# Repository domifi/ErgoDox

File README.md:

# Information
This repo is a fork of the ErgoDox Mechanical Keyboard pcb and Litster's acrylic case designs (both standard and full hand).

This variation of the design has a two main goals:
* Replace the Mini B port with a Type C port while maintaining reversibility of the PCB design.
* Keep the rest of the design as unchanged as possible.
  - The idea is that most case designs should still be compatible (with at most minor adjustments)

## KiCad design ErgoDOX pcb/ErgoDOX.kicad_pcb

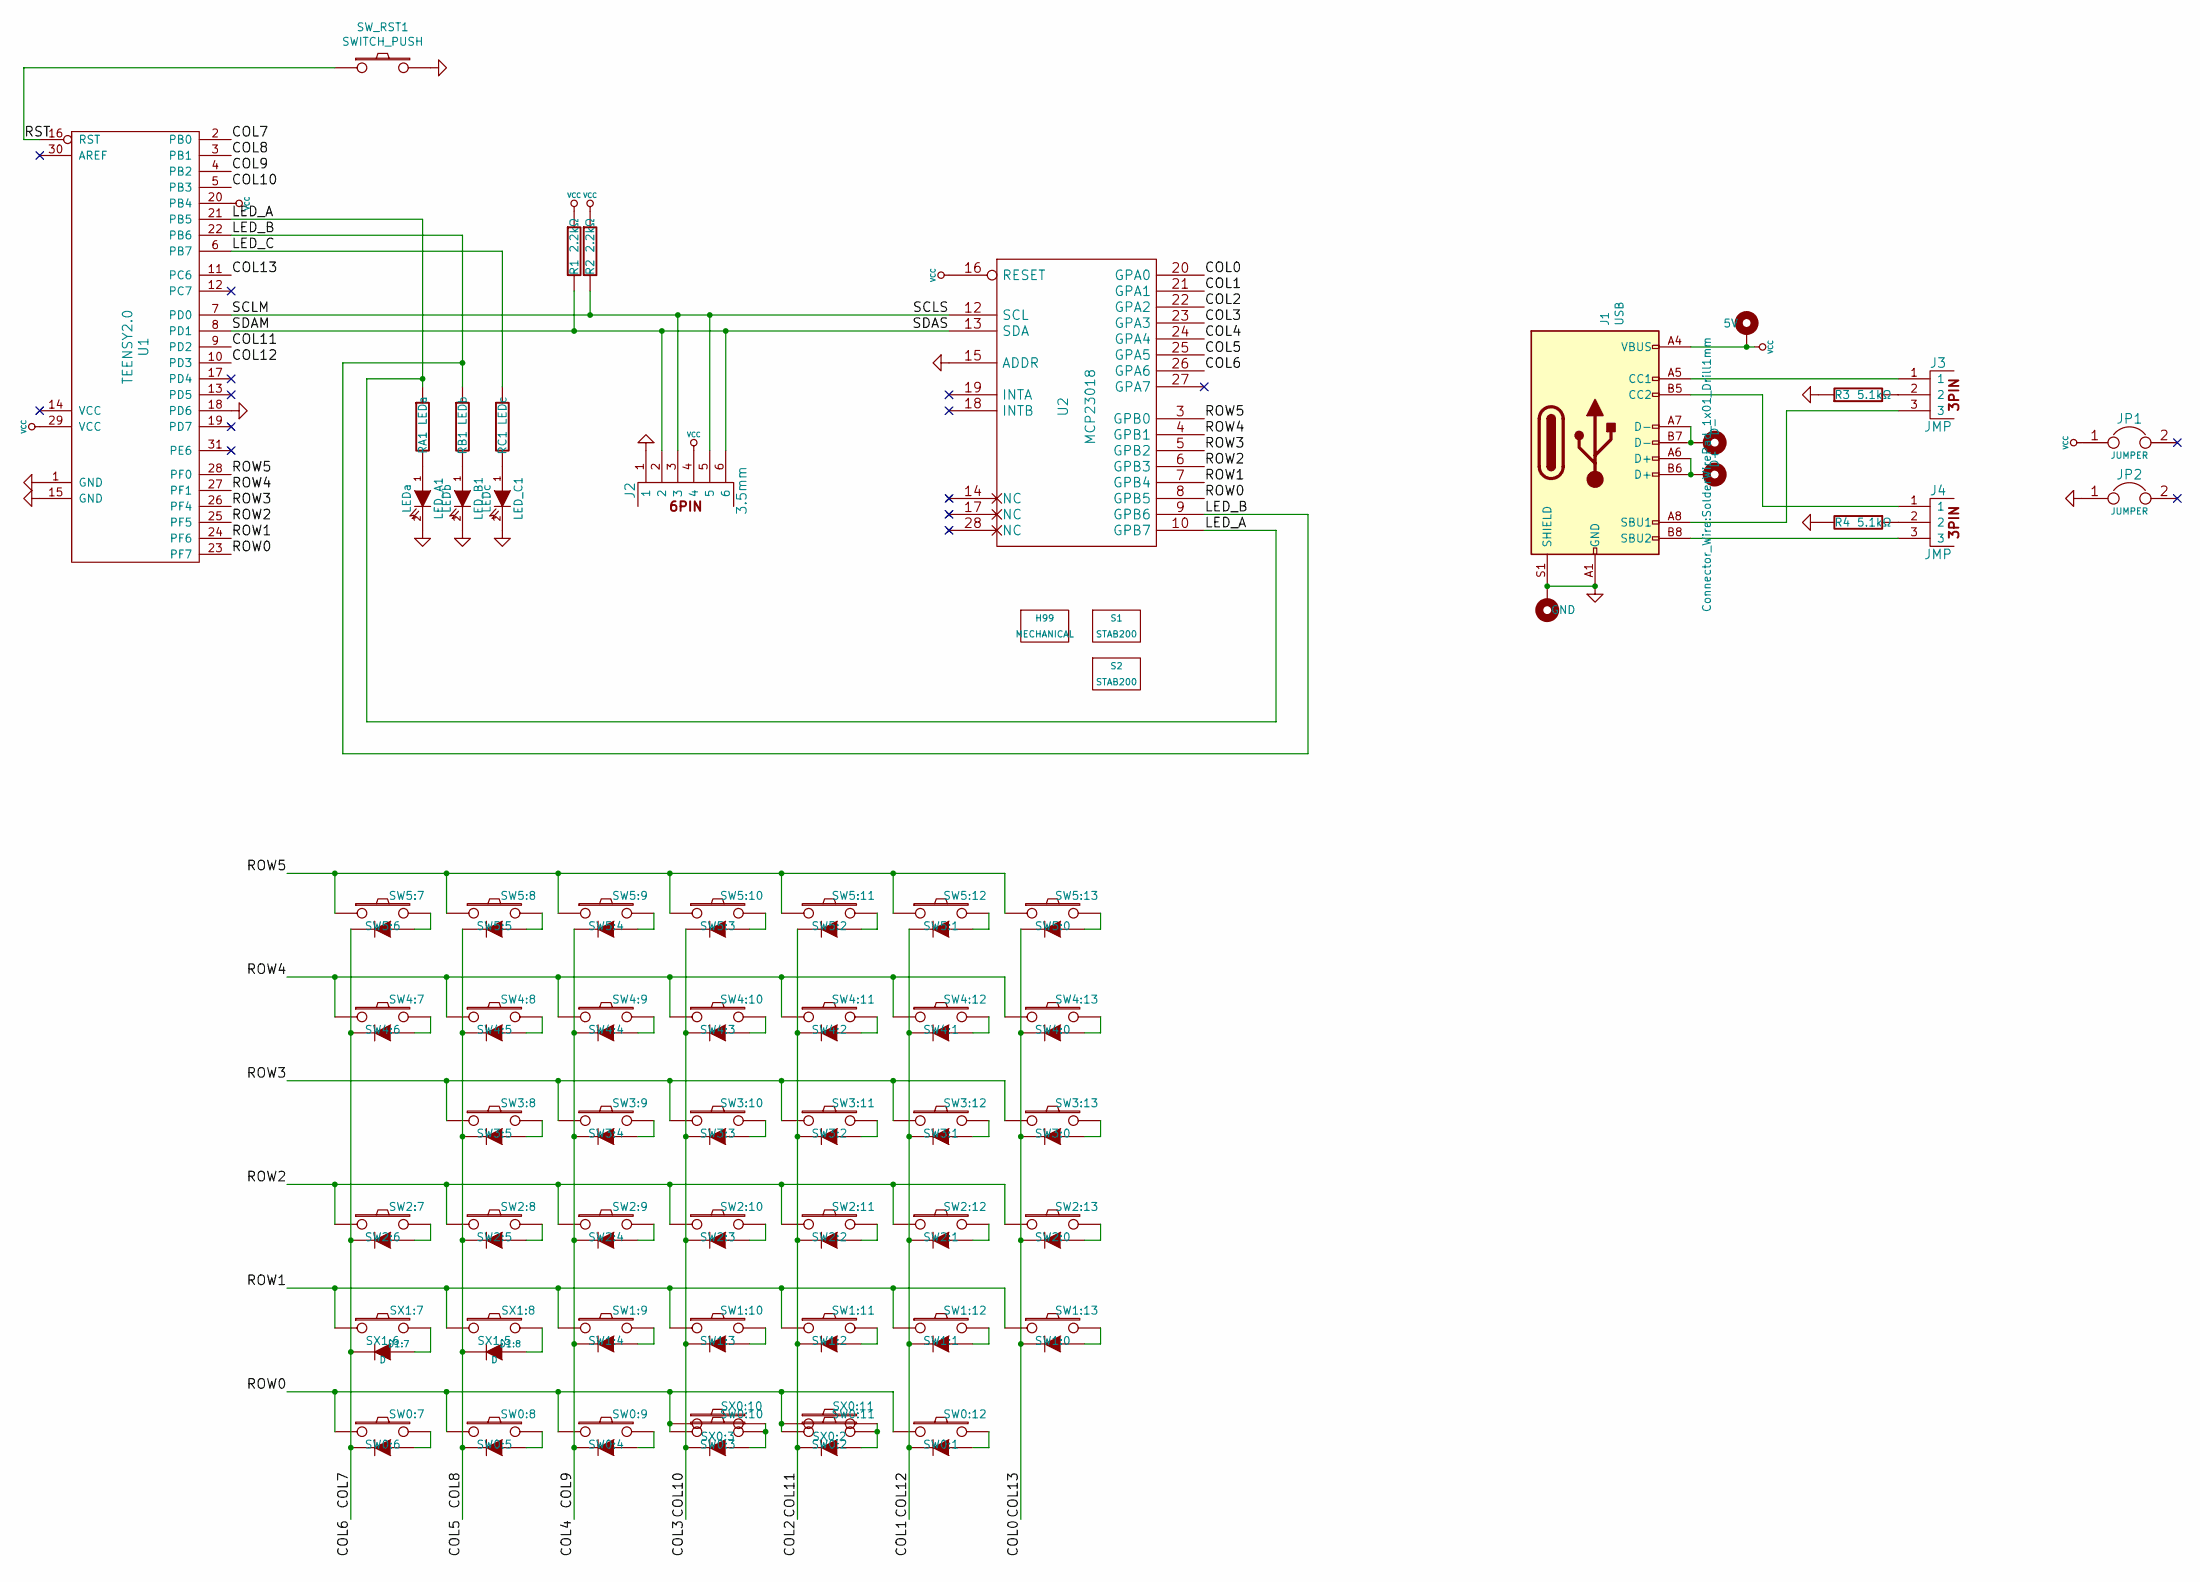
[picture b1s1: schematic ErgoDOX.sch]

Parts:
D1:7, D1:8: D
H1: D+; SolderWirePad_1x01_Drill1mm
H2: D-; SolderWirePad_1x01_Drill1mm
H3: 5V; SolderWirePad_1x01_Drill1mm
H4: GND; SolderWirePad_1x01_Drill1mm
H99: MECHANICAL
J1: USB; USB_C_Receptacle_GCT_USB4085
J2: 3.5mm
J3, J4: JMP
JP1, JP2: JUMPER
LED_A1: LEDa
LED_B1: LEDb
LED_C1: LEDc
R1, R2: 2.2kΩ
R3, R4: 5.1kΩ; R_Axial_DIN0207_L6.3mm_D2.5mm_P10.16mm_Horizontal
RA1: LEDa
RB1: LEDb
RC1: LEDc
S1, S2: STAB200
SW0:7: SW0:6
SW0:8: SW0:5
SW0:9: SW0:4
SW0:10: SW0:3
SW0:11: SW0:2
SW0:12: SW0:1
SW1:9: SW1:4
SW1:10: SW1:3
SW1:11: SW1:2
SW1:12: SW1:1
SW1:13: SW1:0
SW2:7: SW2:6
SW2:8: SW2:5
SW2:9: SW2:4
SW2:10: SW2:3
SW2:11: SW2:2
SW2:12: SW2:1
SW2:13: SW2:0
SW3:8: SW3:5
SW3:9: SW3:4
SW3:10: SW3:3
SW3:11: SW3:2
SW3:12: SW3:1
SW3:13: SW3:0
SW4:7: SW4:6
SW4:8: SW4:5
SW4:9: SW4:4
SW4:10: SW4:3
SW4:11: SW4:2
SW4:12: SW4:1
SW4:13: SW4:0
SW5:7: SW5:6
SW5:8: SW5:5
SW5:9: SW5:4
SW5:10: SW5:3
SW5:11: SW5:2
SW5:12: SW5:1
SW5:13: SW5:0
SW_RST1: SWITCH_PUSH; SW_SPST_B3U-1000P
SX0:10: SX0:3
SX0:11: SX0:2
SX1:7: SX1:6
SX1:8: SX1:5
U1: TEENSY2.0
U2: MCP23018

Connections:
/COL0: SW1:13.4 (K), SW2:13.4 (K), SW3:13.4 (K), SW4:13.4 (K), SW5:13.4 (K), U1.11 (PC6), U2.20 (GPA0)
/COL1: SW0:12.4 (K), SW1:12.4 (K), SW2:12.4 (K), SW3:12.4 (K), SW4:12.4 (K), SW5:12.4 (K), U1.10 (PD3), U2.21 (GPA1)
/COL4: SW0:9.4 (K), SW1:9.4 (K), SW2:9.4 (K), SW3:9.4 (K), SW4:9.4 (K), SW5:9.4 (K), U1.4 (PB2), U2.24 (GPA4)
/COL5: D1:8.2 (K), SW0:8.4 (K), SW2:8.4 (K), SW3:8.4 (K), SW4:8.4 (K), SW5:8.4 (K), U1.3 (PB1), U2.25 (GPA5)
/COL6: D1:7.2 (K), SW0:7.4 (K), SW2:7.4 (K), SW4:7.4 (K), SW5:7.4 (K), U1.2 (PB0), U2.26 (GPA6)
/COL10: SW0:10.4 (K), SW1:10.4 (K), SW2:10.4 (K), SW3:10.4 (K), SW4:10.4 (K), SW5:10.4 (K), U1.5 (PB3), U2.23 (GPA3)
/COL11: SW0:11.4 (K), SW1:11.4 (K), SW2:11.4 (K), SW3:11.4 (K), SW4:11.4 (K), SW5:11.4 (K), U1.9 (PD2), U2.22 (GPA2)
/LED_A: RA1.1, U1.21 (PB5), U2.10 (GPB7)
/LED_B: RB1.1, U1.22 (PB6), U2.9 (GPB6)
/LED_C: RC1.1, U1.6 (PB7)
/ROW0: SW0:7.1, SW0:8.1, SW0:9.1, SW0:10.1, SW0:11.1, SW0:12.1, SX0:10.1, SX0:11.1, U1.23 (PF7), U2.8 (GPB5)
/ROW1: SW1:9.1, SW1:10.1, SW1:11.1, SW1:12.1, SW1:13.1, SX1:7.1, SX1:8.1, U1.24 (PF6), U2.7 (GPB4)
/ROW2: SW2:7.1, SW2:8.1, SW2:9.1, SW2:10.1, SW2:11.1, SW2:12.1, SW2:13.1, U1.25 (PF5), U2.6 (GPB3)
/ROW3: SW3:8.1, SW3:9.1, SW3:10.1, SW3:11.1, SW3:12.1, SW3:13.1, U1.26 (PF4), U2.5 (GPB2)
/ROW4: SW4:7.1, SW4:8.1, SW4:9.1, SW4:10.1, SW4:11.1, SW4:12.1, SW4:13.1, U1.27 (PF1), U2.4 (GPB1)
/ROW5: SW5:7.1, SW5:8.1, SW5:9.1, SW5:10.1, SW5:11.1, SW5:12.1, SW5:13.1, U1.28 (PF0), U2.3 (GPB0)
/RST: SW_RST1.1, U1.16 (RST)
/SCLM: J2.3, J2.5, R2.2, U1.7 (PD0), U2.12 (SCL)
/SDAM: J2.2, J2.6, R1.2, U1.8 (PD1), U2.13 (SDA)
GND: H4.1, J1.A1 (GND), J1.A12 (GND), J1.B1 (GND), J1.B12 (GND), J1.S1 (SHIELD), J2.1, JP2.1, LED_A1.2 (K), LED_B1.2 (K), LED_C1.2 (K), R3.1, R4.2, SW_RST1.2, U1.1 (GND), U1.15 (GND), U1.18 (PD6), U2.1 (GND), U2.15 (ADDR)
unnamed: D1:7.1 (A), SX1:7.2
unnamed: D1:8.1 (A), SX1:8.2
unnamed: H1.1, J1.A6 (D+), J1.B6 (D+)
unnamed: H2.1, J1.A7 (D-), J1.B7 (D-)
unnamed: J1.A5 (CC1), J3.1
unnamed: J1.A8 (SBU1), J3.3
unnamed: J1.B5 (CC2), J4.1
unnamed: J1.B8 (SBU2), J4.3
unnamed: J3.2, R3.2
unnamed: J4.2, R4.1
unnamed: LED_A1.1 (A), RA1.2
unnamed: LED_B1.1 (A), RB1.2
unnamed: LED_C1.1 (A), RC1.2
unnamed: SW0:7.2, SW0:7.3 (A)
unnamed: SW0:8.2, SW0:8.3 (A)
unnamed: SW0:9.2, SW0:9.3 (A)
unnamed: SW0:10.2, SW0:10.3 (A), SX0:10.2
unnamed: SW0:11.2, SW0:11.3 (A), SX0:11.2
unnamed: SW0:12.2, SW0:12.3 (A)
unnamed: SW1:9.2, SW1:9.3 (A)
unnamed: SW1:10.2, SW1:10.3 (A)
unnamed: SW1:11.2, SW1:11.3 (A)
unnamed: SW1:12.2, SW1:12.3 (A)
unnamed: SW1:13.2, SW1:13.3 (A)
unnamed: SW2:7.2, SW2:7.3 (A)
unnamed: SW2:8.2, SW2:8.3 (A)
unnamed: SW2:9.2, SW2:9.3 (A)
unnamed: SW2:10.2, SW2:10.3 (A)
unnamed: SW2:11.2, SW2:11.3 (A)
unnamed: SW2:12.2, SW2:12.3 (A)
unnamed: SW2:13.2, SW2:13.3 (A)
unnamed: SW3:8.2, SW3:8.3 (A)
unnamed: SW3:9.2, SW3:9.3 (A)
unnamed: SW3:10.2, SW3:10.3 (A)
unnamed: SW3:11.2, SW3:11.3 (A)
unnamed: SW3:12.2, SW3:12.3 (A)
unnamed: SW3:13.2, SW3:13.3 (A)
unnamed: SW4:7.2, SW4:7.3 (A)
unnamed: SW4:8.2, SW4:8.3 (A)
unnamed: SW4:9.2, SW4:9.3 (A)
unnamed: SW4:10.2, SW4:10.3 (A)
unnamed: SW4:11.2, SW4:11.3 (A)
unnamed: SW4:12.2, SW4:12.3 (A)
unnamed: SW4:13.2, SW4:13.3 (A)
unnamed: SW5:7.2, SW5:7.3 (A)
unnamed: SW5:8.2, SW5:8.3 (A)
unnamed: SW5:9.2, SW5:9.3 (A)
unnamed: SW5:10.2, SW5:10.3 (A)
unnamed: SW5:11.2, SW5:11.3 (A)
unnamed: SW5:12.2, SW5:12.3 (A)
unnamed: SW5:13.2, SW5:13.3 (A)
VCC: H3.1, J1.A4 (VBUS), J1.A9 (VBUS), J1.B4 (VBUS), J1.B9 (VBUS), J2.4, JP1.1, R1.1, R2.1, U1.20 (PB4), U1.29 (VCC), U2.11 (VCC), U2.16 (RESET)

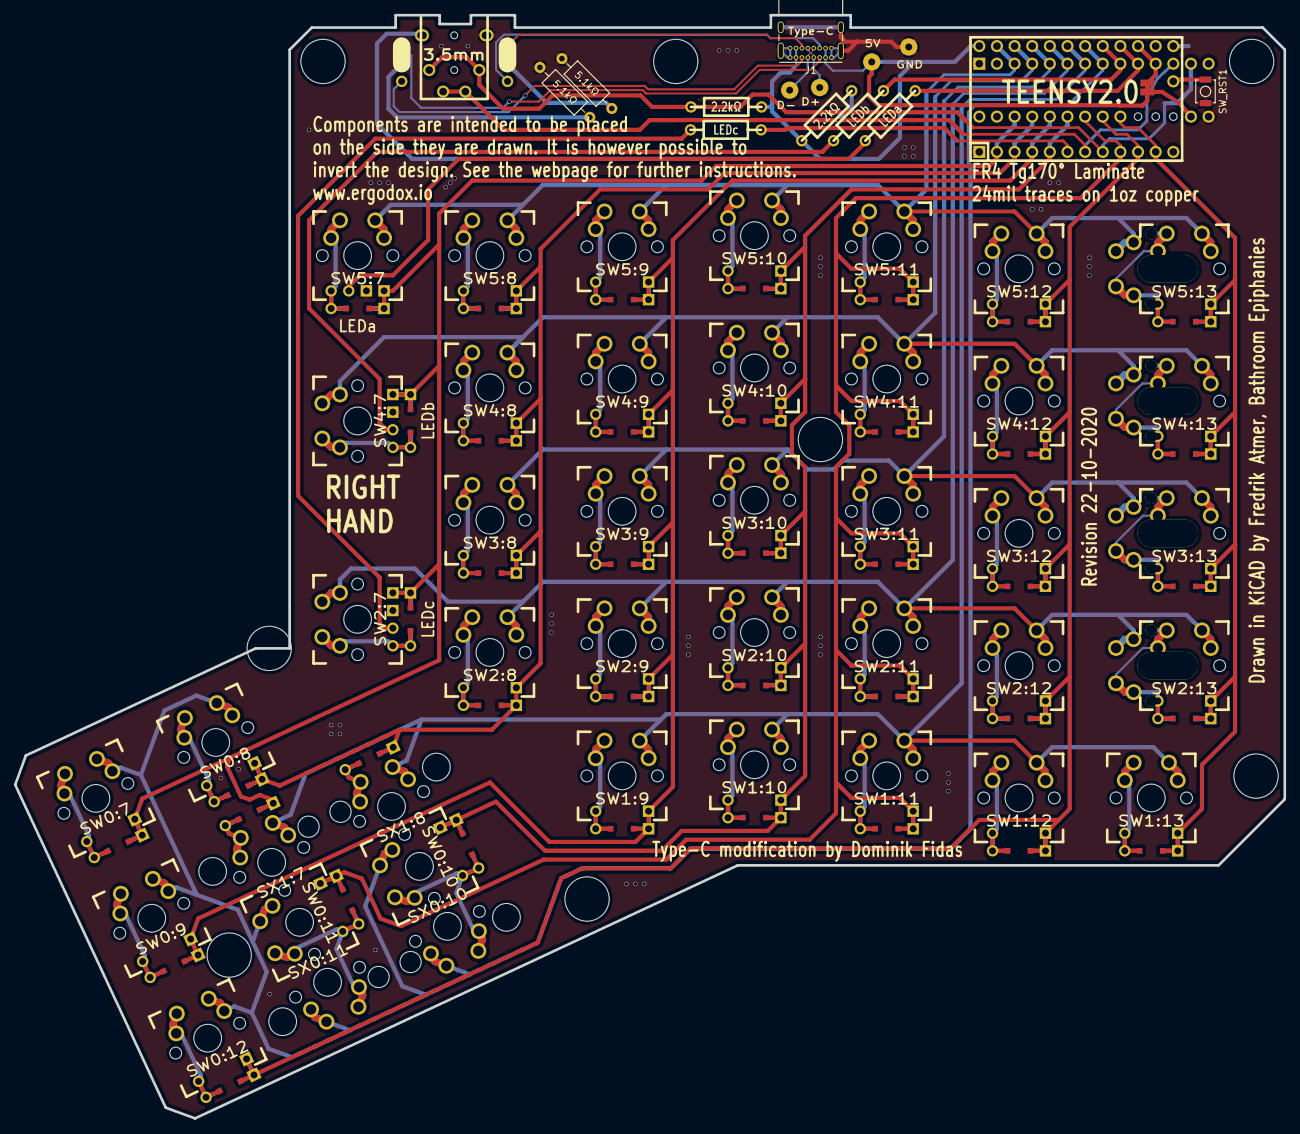
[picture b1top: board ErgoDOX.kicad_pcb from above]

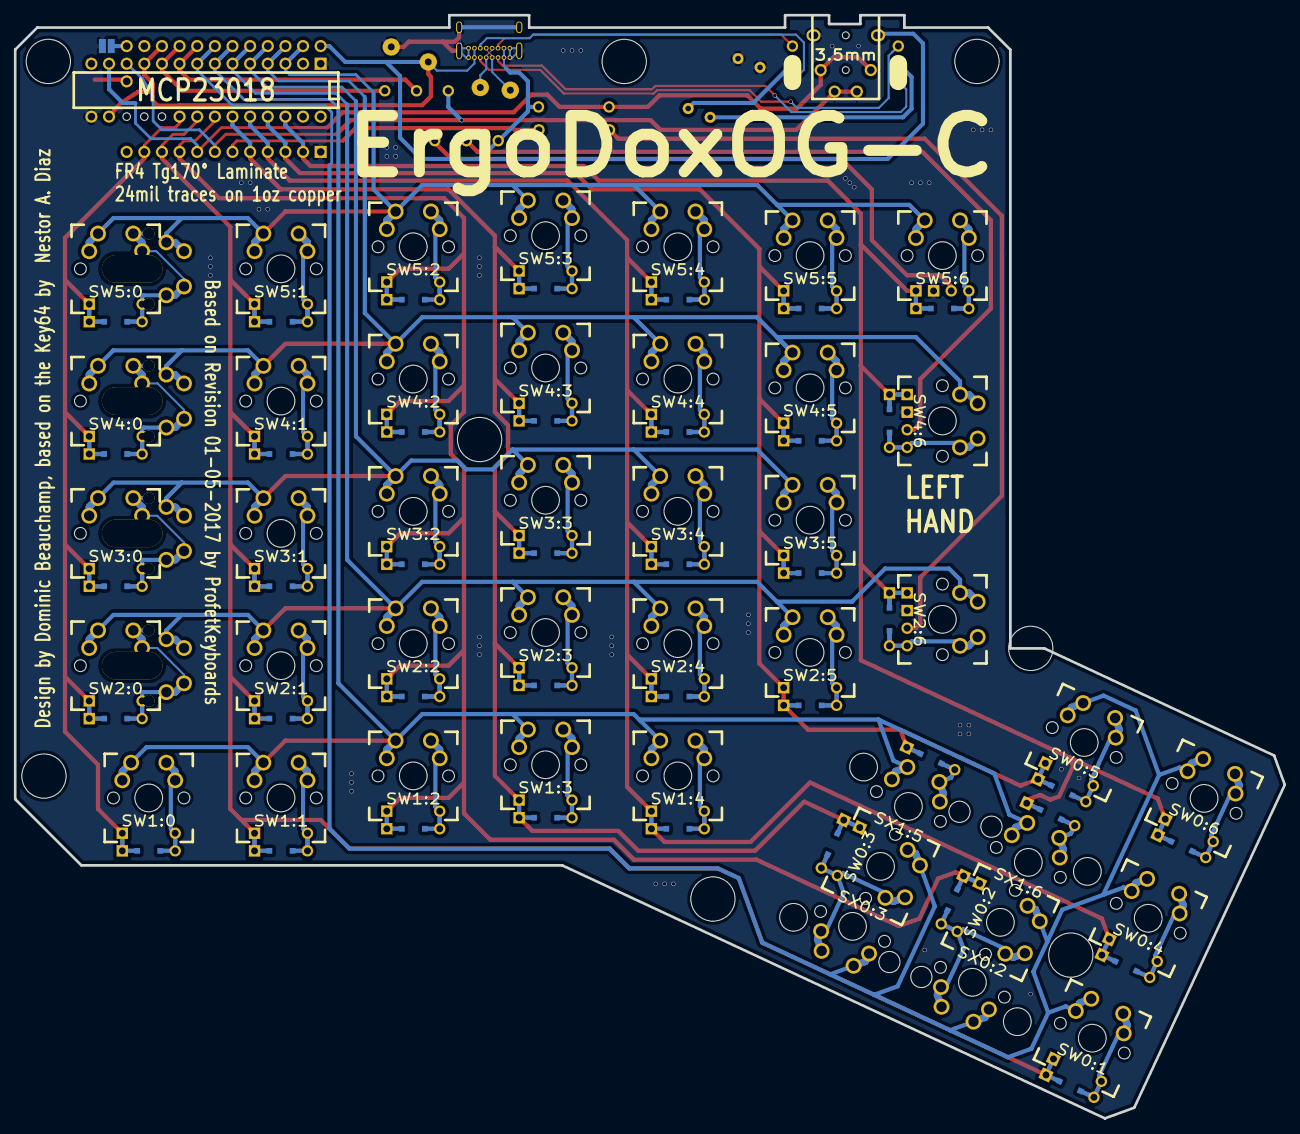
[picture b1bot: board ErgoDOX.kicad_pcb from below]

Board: 2 copper layers, 182.8 x 158.9 mm, 70 parts (3 on the bottom side), 72 nets.

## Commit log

2020-10-18 added usb c to schema
2020-10-19 probably done
2020-10-19 added an apparently important cache file back
2020-10-20 rearranged components to maximize case compatibility
2020-10-22 added licence
2020-10-24 added script for panelization with KiKit
2020-10-24 updated gitignore
2020-10-24 updated silkscreen
2020-10-24 brought gerber files to current state
